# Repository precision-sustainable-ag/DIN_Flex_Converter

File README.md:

# DIN_Flex_Converter
A DIN rail mountable, Adjustable DC-DC converter for Common Low Voltage Conversions

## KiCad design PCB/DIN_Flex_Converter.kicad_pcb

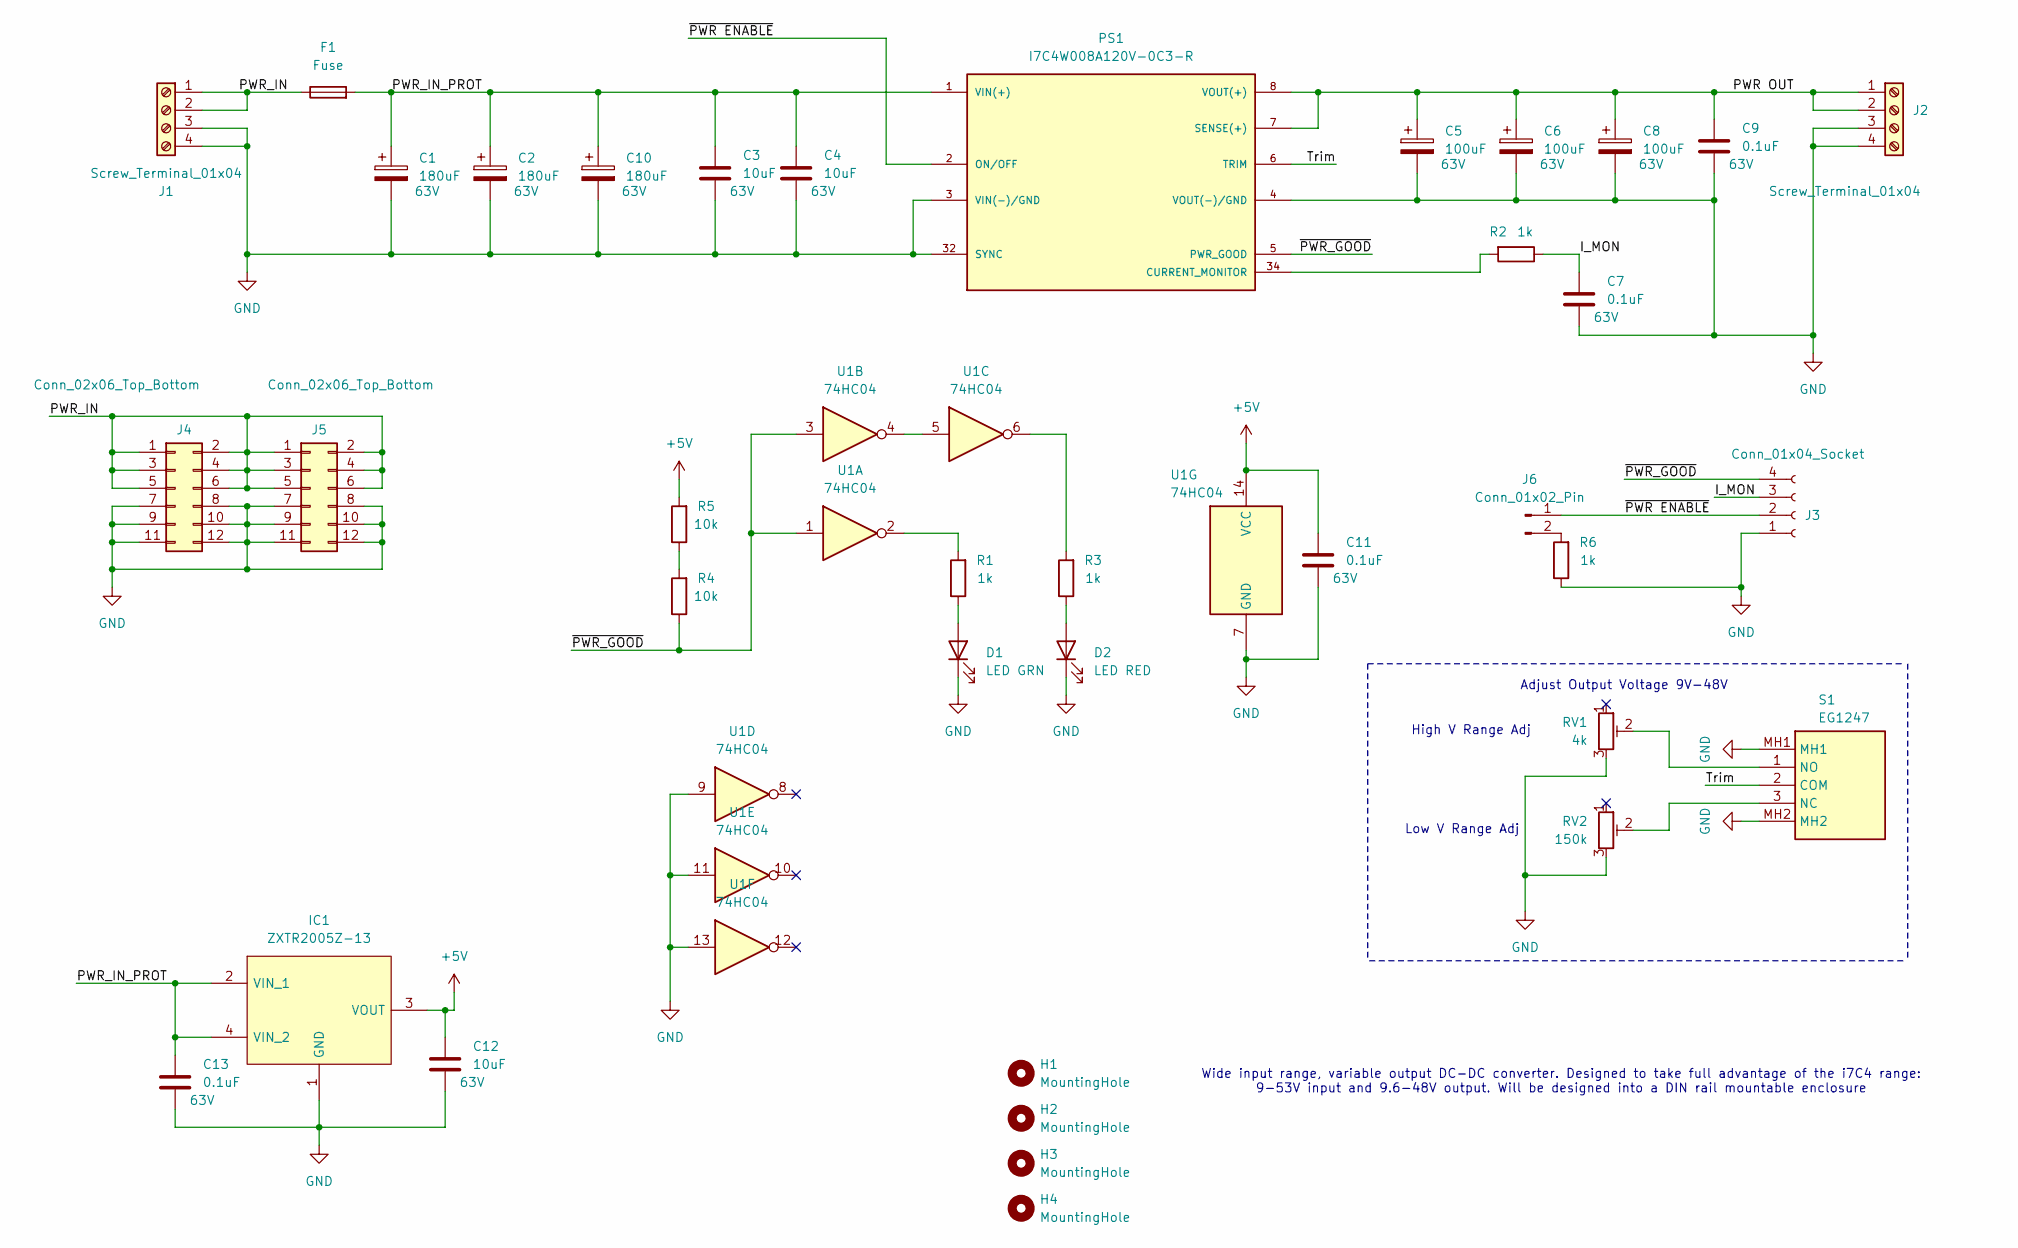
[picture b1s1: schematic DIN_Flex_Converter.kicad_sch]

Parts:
C1, C2, C10: 180uF; CP_Elec_10x12.6; Voltage 63V
C3, C4, C12: 10uF; C_1210_3225Metric; Voltage 63V
C5, C6, C8: 100uF; CP_Elec_10x12.6; Voltage 63V
C7, C9, C11, C13: 0.1uF; C_1206_3216Metric; Voltage 63V
D1: LED GRN; LED_155124RV73200
D2: LED RED; LED_155124RV73200
F1: Fuse; FUSC9830X318N
H1, H2, H3, H4: MountingHole; MountingHole_3.2mm_M3_DIN965
IC1: ZXTR2005Z-13; AZ7042RTRG1; Mouser Part Number 621-ZXTR2005Z-13
J1: Screw_Terminal_01x04; PHOENIX_2907774
J2: Screw_Terminal_01x04; PHOENIX_2907787
J3: Conn_01x04_Socket; PHOENIX_1803293
J4, J5: Conn_02x06_Top_Bottom; SSM-106-XXX-DV
J6: Conn_01x02_Pin; PinHeader_1x02_P2.54mm_Vertical
PS1: I7C4W008A120V-0C3-R; CONV_I7C4W008A120V-0C3-R
R1, R2, R3, R6: 1k; R_1206_3216Metric
R4, R5: 10k; R_1206_3216Metric
RV1: 4k; 3009P1154LF
RV2: 150k; 3009P1154LF
S1: EG1247; Mouser Part Number 612-EG1247
U1: 74HC04; SOIC127P600X175-14N

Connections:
+5V: C11.1, C12.1, IC1.3 (VOUT), R5.2, U1.14 (VCC)
/I_MON: C7.1, J3.3, R2.1
/PWR OUT: C5.1, C6.1, C8.1, C9.1, J2.1, J2.2, PS1.7 (SENSE(+)), PS1.8 (VOUT(+))
/PWR_IN: F1.1, J1.1, J1.2, J4.1, J4.2, J4.3, J4.4, J4.5, J4.6, J5.1, J5.2, J5.3, J5.4, J5.5, J5.6
/PWR_IN_PROT: C1.1, C2.1, C3.1, C4.1, C10.1, C13.1, F1.2, IC1.2 (VIN_1), IC1.4 (VIN_2), PS1.1 (VIN(+))
/Trim: PS1.6 (TRIM), S1.2 (COM)
/~PWR ENABLE: J3.2, J6.1, PS1.2 (ON/OFF); also elsewhere on the board
/~PWR_GOOD: J3.4, PS1.5 (PWR_GOOD), R4.1, U1.1, U1.3
GND: C1.2, C2.2, C3.2, C4.2, C5.2, C6.2, C7.2, C8.2, C9.2, C10.2, C11.2, C12.2, C13.2, D1.1 (K), D2.1 (K), IC1.1 (GND), J1.3, J1.4, J2.3, J2.4, J3.1, J4.7, J4.8, J4.9, J4.10, J4.11, J4.12, J5.7, J5.8, J5.9, J5.10, J5.11, J5.12, PS1.3 (VIN(-)/GND), PS1.4 (VOUT(-)/GND), PS1.32 (SYNC), R6.1, RV1.3, RV2.3, S1.MH1, S1.MH2, U1.7 (GND), U1.9, U1.11, U1.13
unnamed: D1.2 (A), R1.1
unnamed: D2.2 (A), R3.1
unnamed 11: J6.2, R6.2; also elsewhere on the board
unnamed: PS1.34 (CURRENT_MONITOR), R2.2
unnamed: R1.2, U1.2
unnamed: R3.2, U1.6
unnamed: R4.2, R5.1
unnamed: RV2.2, S1.3 (NC)
unnamed: RV1.2, S1.1 (NO)
unnamed: U1.4, U1.5

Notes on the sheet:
Adjust Output Voltage 9V-48V
High V Range Adj
Low V Range Adj
Wide input range, variable output DC-DC converter. Designed to take full advantage of the i7C4 range: 9-53V input and 9.6-48V output. Will be designed into a DIN rail mountable enclosure

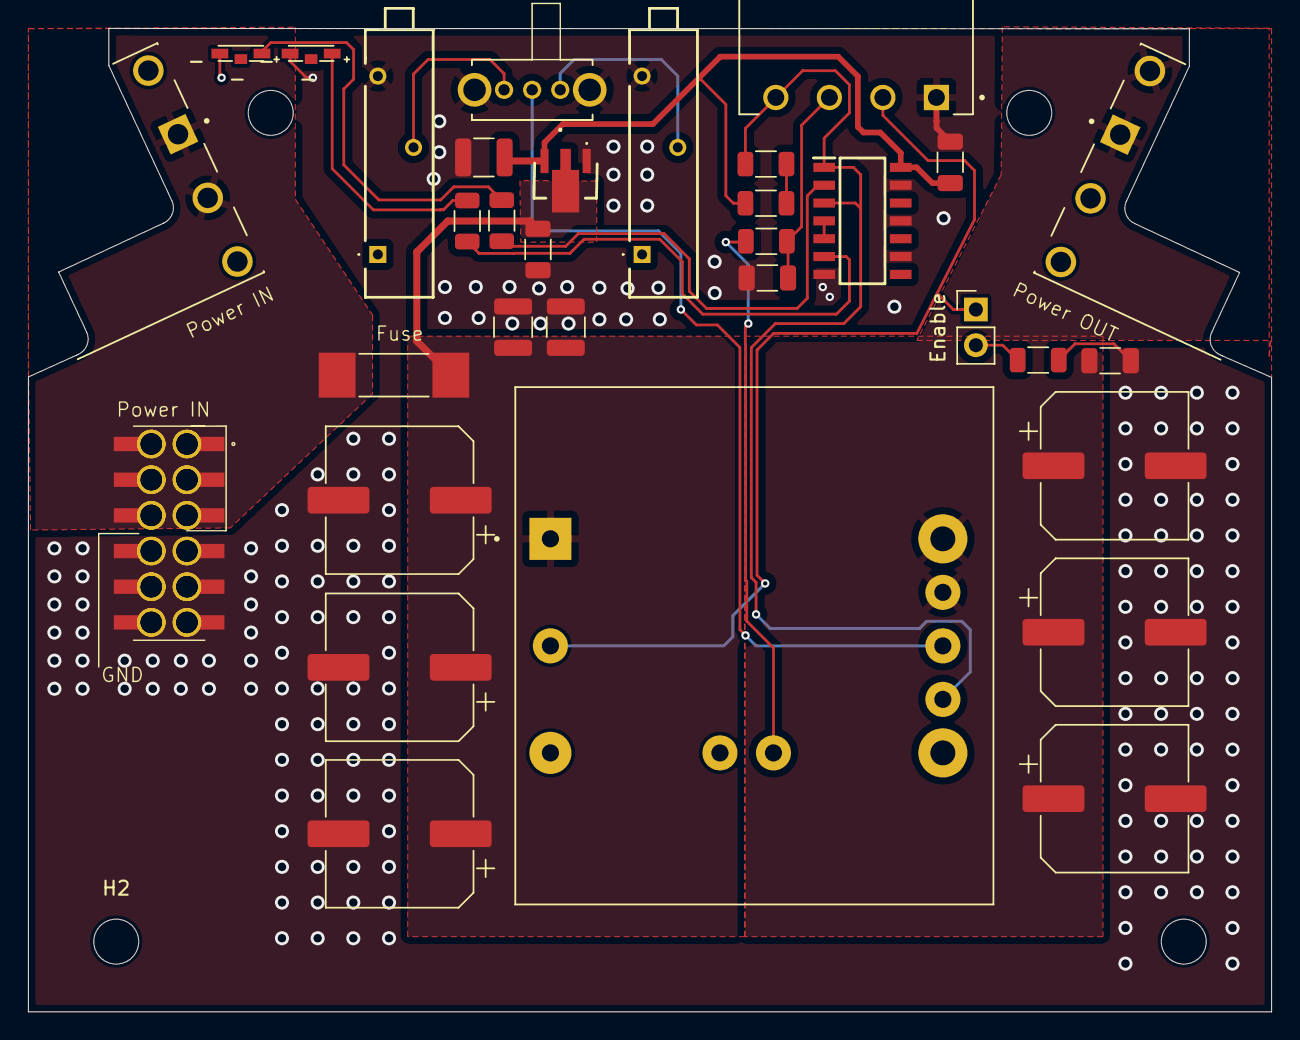
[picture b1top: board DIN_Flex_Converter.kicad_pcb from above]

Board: 2 copper layers, 88.5 x 70.0 mm, 38 parts (1 on the bottom side), 19 nets.

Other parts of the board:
Enable: Conn_01x02_Pin; PinHeader_1x02_P2.54mm_Vertical

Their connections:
/~PWR ENABLE: Enable.1; also elsewhere on the board
unnamed 11: Enable.2; also elsewhere on the board

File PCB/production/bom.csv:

Designator,Footprint,Quantity,Value,LCSC Part #
"C1, C10, C2",CP_Elec_10x12.6,3,180uF,
"C11, C13, C7, C9",1206,4,0.1uF,
"C12, C3, C4",1210,3,10uF,
"C5, C6, C8",CP_Elec_10x12.6,3,100uF,
D1,LED_155124RV73200,1,LED GRN,
D2,LED_155124RV73200,1,LED RED,
F1,FUSC9830X318N,1,Fuse,
IC1,AZ7042RTRG1,1,ZXTR2005Z-13,
J1,PHOENIX_2907774,1,Screw_Terminal_01x04,
J2,PHOENIX_2907787,1,Screw_Terminal_01x04,
J3,PHOENIX_1803293,1,Conn_01x04_Socket,
"J4, J5",SSM-106-XXX-DV,2,Conn_02x06_Top_Bottom,
PS1,CONV_I7C4W008A120V-0C3-R,1,I7C4W008A120V-0C3-R,
"R1, R2, R3",1206,3,1k,
"R4, R5",1206,2,10k,
RV1,3009P1154LF,1,4k,
RV2,3009P1154LF,1,150k,
S1,EG1247,1,EG1247,
U1,SOIC127P600X175-14N,1,74HC04,

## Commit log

2024-05-06 added ignor lists
2024-05-06 Inital DC to DC module schematic
2024-05-06 Added Trim & Linear Regulator
2024-05-06 Added Indication Ckt to Schematic
2024-05-07 Draft Schematic & Layout
2024-05-08 Enclosure Draft
2024-05-08 Layout & Route Draft Complete
2024-05-08 PCB Finalized and manufacturing files generated
2024-05-08 Exported 3D PCBA from KiCad & Imported into SW
2024-05-08 V1 Design Complete, all parts ordered.
2024-06-21 fixed LED footprint/routing and added enable jumper
2025-08-22 Add PnP File For SMD Assembly on LumenPnP
